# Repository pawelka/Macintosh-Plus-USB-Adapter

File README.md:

# Macintosh Plus USB Keyboard and Mouse Adapter

Firmware for a CH554-based USB host adapter that lets a Macintosh Plus, 512K, or 128K use a modern USB HID keyboard and mouse.

The adapter enumerates a USB HID boot keyboard and/or boot mouse, translates keyboard reports to Macintosh keyboard protocol transitions, and converts USB mouse movement to Macintosh quadrature mouse signals.

## Current Status

This project is at working-prototype stage. A PCB is still TODO.

## Supported Devices

- USB HID boot-protocol keyboards.
- USB HID boot-protocol mice.
- Composite keyboard/mouse receivers, such as many 2.4 GHz wireless dongles.
- A keyboard-only or mouse-only device.

The CH554 firmware handles one USB device on the root host port. If the keyboard and mouse are separate USB devices, use a combined receiver or build two adapters.

## Hardware Notes

The firmware targets a WCH CH554 running at 16 MHz.

Configured signal pins:

| DB9 pin| CH554 pin | Function |
| --- | --- | --- |
| N/A | P3.3 | Macintosh keyboard DATA |
| N/A | P3.4 | Macintosh keyboard CLOCK |
| 4 | P1.4 | Mouse X1 quadrature |
| 5 | P1.1 | Mouse X0 quadrature |
| 9 | P1.6 | Mouse Y0 quadrature |
| 8 | P1.7 | Mouse Y1 quadrature |
| 7 | P1.5 | Mouse button |
| N/A | P3.2 | USB/device status LED, active low |
| N/A | P3.1 | Optional UART0 TX debug output |
| N/A | P3.0 | Optional UART0 RX debug output |

Debug serial, when enabled, is UART0 TX on P3.1 at 9600 8N1.

## Building

Install PlatformIO, then install the project Python dependency into PlatformIO's Python environment.
On macOS or Linux:

```sh
~/.platformio/penv/bin/python -m pip install -r requirements-pio.txt
```

On Windows:

```powershell
& "$env:USERPROFILE\.platformio\penv\Scripts\python.exe" -m pip install -r requirements-pio.txt
```

Build the firmware:

```sh
pio run
```

## Flashing

The default upload command converts the Intel HEX output to `firmware.bin`, then flashes it with `ch55xtool.py`:

```sh
pio run -t upload
```

`ch55xtool.py` requires PyUSB and a native libusb backend. Both are provided by
the packages listed in `requirements-pio.txt`.

An alternate `wchisptool` upload command is kept in `platformio.ini` as a commented reference.

## Debug Logging

Serial debug logging is disabled by default:

```ini
-DDEBUG_SERIAL=0
```

To enable logs on UART0 TX P3.1 at 9600 8N1, change the build flag in `platformio.ini`:

```ini
-DDEBUG_SERIAL=1
```

## Credits

This project is inspired by [jjmz/Atari-Quadrature-USB-Mouse-Adapter](https://github.com/jjmz/Atari-Quadrature-USB-Mouse-Adapter). The mouse quadrature code and early CH554 programming references were derived from that project.

The USB host code is based on WCH CH554 examples, adapted for this adapter.

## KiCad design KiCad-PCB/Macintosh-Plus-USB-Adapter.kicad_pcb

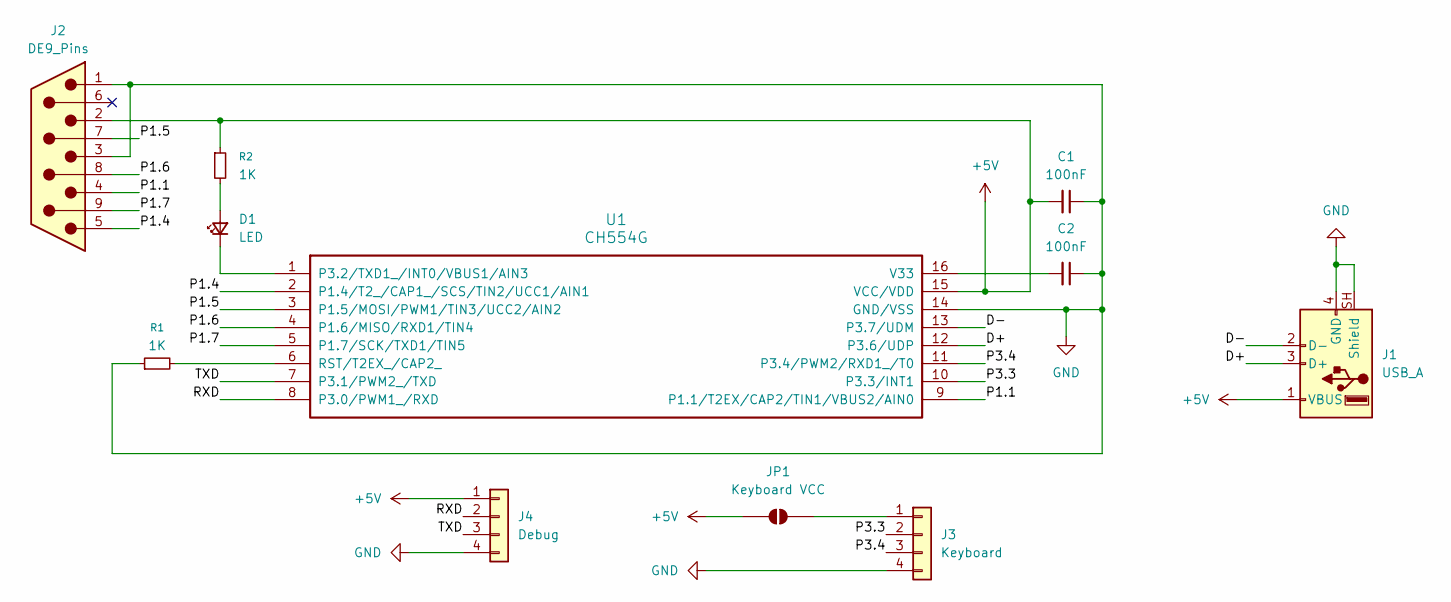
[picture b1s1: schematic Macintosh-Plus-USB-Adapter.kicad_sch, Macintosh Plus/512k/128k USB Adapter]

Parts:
C1, C2: 100nF; C_0805_2012Metric_Pad1.18x1.45mm_HandSolder
D1: LED; LED_0805_2012Metric
J1: USB_A; USB_A_TE_292303-7_Horizontal
J2: DE9_Pins; DSUB-9_Pins_EdgeMount_P2.77mm
J3: Keyboard; PinHeader_1x04_P1.00mm_Vertical
J4: Debug; PinHeader_1x04_P1.00mm_Vertical
JP1: Keyboard VCC; SolderJumper-2_P1.3mm_Open_Pad1.0x1.5mm
R1, R2: 1K; R_0805_2012Metric_Pad1.20x1.40mm_HandSolder
U1: CH554G; STC_SOP-16_3.9x9.9mm_P1.27mm

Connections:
+5V: C1.2, J1.1 (VBUS), J2.2, J4.1, JP1.1 (A), R2.1, U1.15 (VCC/VDD)
/D+: J1.3 (D+), U1.12 (P3.6/UDP)
/D-: J1.2 (D-), U1.13 (P3.7/UDM)
/P1.1: J2.4, U1.9 (P1.1/T2EX/CAP2/TIN1/VBUS2/AIN0)
/P1.4: J2.5, U1.2 (P1.4/T2_/CAP1_/SCS/TIN2/UCC1/AIN1)
/P1.5: J2.7, U1.3 (P1.5/MOSI/PWM1/TIN3/UCC2/AIN2)
/P1.6: J2.8, U1.4 (P1.6/MISO/RXD1/TIN4)
/P1.7: J2.9, U1.5 (P1.7/SCK/TXD1/TIN5)
/P3.3: J3.2, U1.10 (P3.3/INT1)
/P3.4: J3.3, U1.11 (P3.4/PWM2/RXD1_/T0)
/RXD: J4.2, U1.8 (P3.0/PWM1_/RXD)
/TXD: J4.3, U1.7 (P3.1/PWM2_/TXD)
GND: C1.1, C2.1, J1.4 (GND), J1.SH (Shield), J2.1, J2.3, J3.4, J4.4, R1.1, U1.14 (GND/VSS)
unnamed: D1.2 (A), R2.2
unnamed: D1.1 (K), U1.1 (P3.2/TXD1_/INT0/VBUS1/AIN3)
unnamed: J3.1, JP1.2 (B)
unnamed: R1.2, U1.6 (RST/T2EX_/CAP2_)
unnamed: C2.2, U1.16 (V33)

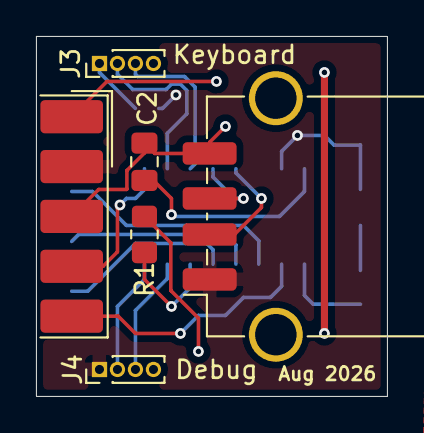
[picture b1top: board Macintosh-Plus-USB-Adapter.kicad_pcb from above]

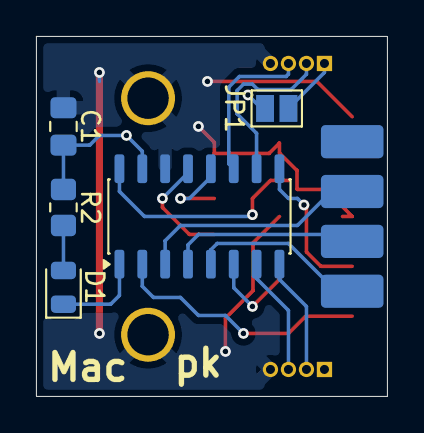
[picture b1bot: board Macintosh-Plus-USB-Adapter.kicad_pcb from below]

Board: 2 copper layers, 19.5 x 20.0 mm, 11 parts (5 on the bottom side), 18 nets.
